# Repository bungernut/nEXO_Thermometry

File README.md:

# nNEXO_Microcontroller_Temp
Using Teensy 4.1 and Arduino Mega to collect temperatures using PT100's and thermocouples

This program requires several libraries to be compiled. 
All but the WDT is installable via the Arduino library manager. 
Since the project is built on a Teensy4.1 it also naturally also reduires Teensyduino.
- [ ] Adafruit BME280
- [ ] Adafruit MAX31865
- [ ] Adafruit MAX31856
- [ ] WDT_T4 (https://github.com/tonton81/WDT_T4)

Current TODO:
- Fix NativeEthernet locking issue
- Prevent LCD burn in (partially done)
- Issue with assigning IP to multiple devices, should have put a couple dip switches to assign mac or IP

Future feature adds:
- Utilize ILI9341 touch feature for interactive display

Schematic of PCB

PCBnew

PCB Version 1.2  
https://oshpark.com/shared_projects/bG9Ms06A (untested)

Parts:

| LOC | Part | Digikey PN |
| -- | -- | -- |
| J1 |  DB15 | LD15S33E4GV00LF-ND |
| J2 | Barrel 2x5.5mm | CP-002A-ND |
|Teensy Conn| 24POS RCPT| SAM1093-24-ND|
|Teensy Conn| 6POS 2mm RCPT| DUPIIN - 2141-2X03G00SB |
|Teensy header| 30POS 2.54mm | S1012EC-30-ND |
|Teensy header| 6POS 2mm | WM20513-ND |
| Ethernet Conn | 100 Base T | 1278-1052-ND |
| LCD Conn | 2x CONN HEADER 14POS | AE11367-ND|
| R1-12 | 22 Ohm 0805 | A126437CT-ND |
| R13 | 0 Ohm 0805 | A106066CT-ND |
| CP1 | 47 uF 1206 | 490-16309-1-ND |
| F1 | 1A Fuse | F6777CT-ND |
| C1 | 0.1 uF Ethernet Cap | BC1084CT-ND |
| MCU1 | 2x 24POS Recpt | SAM1093-24-ND |

### - Sensor Boards
| Board Type | Purpose | Digikey Pin |
| -- | -- | -- |
| Adafruit MAX31865 | RTD | 1528-1804-ND |
| Adafruit MAX31856 | Thermocouple Amplifier | 1528-1772-ND |
| Adafruit BME 280 | Temperature, Humidity, Pressure | 1528-1359-ND |

### - Microcontroller

Teensy 4.1 -
  - 1568-DEV-16771-ND

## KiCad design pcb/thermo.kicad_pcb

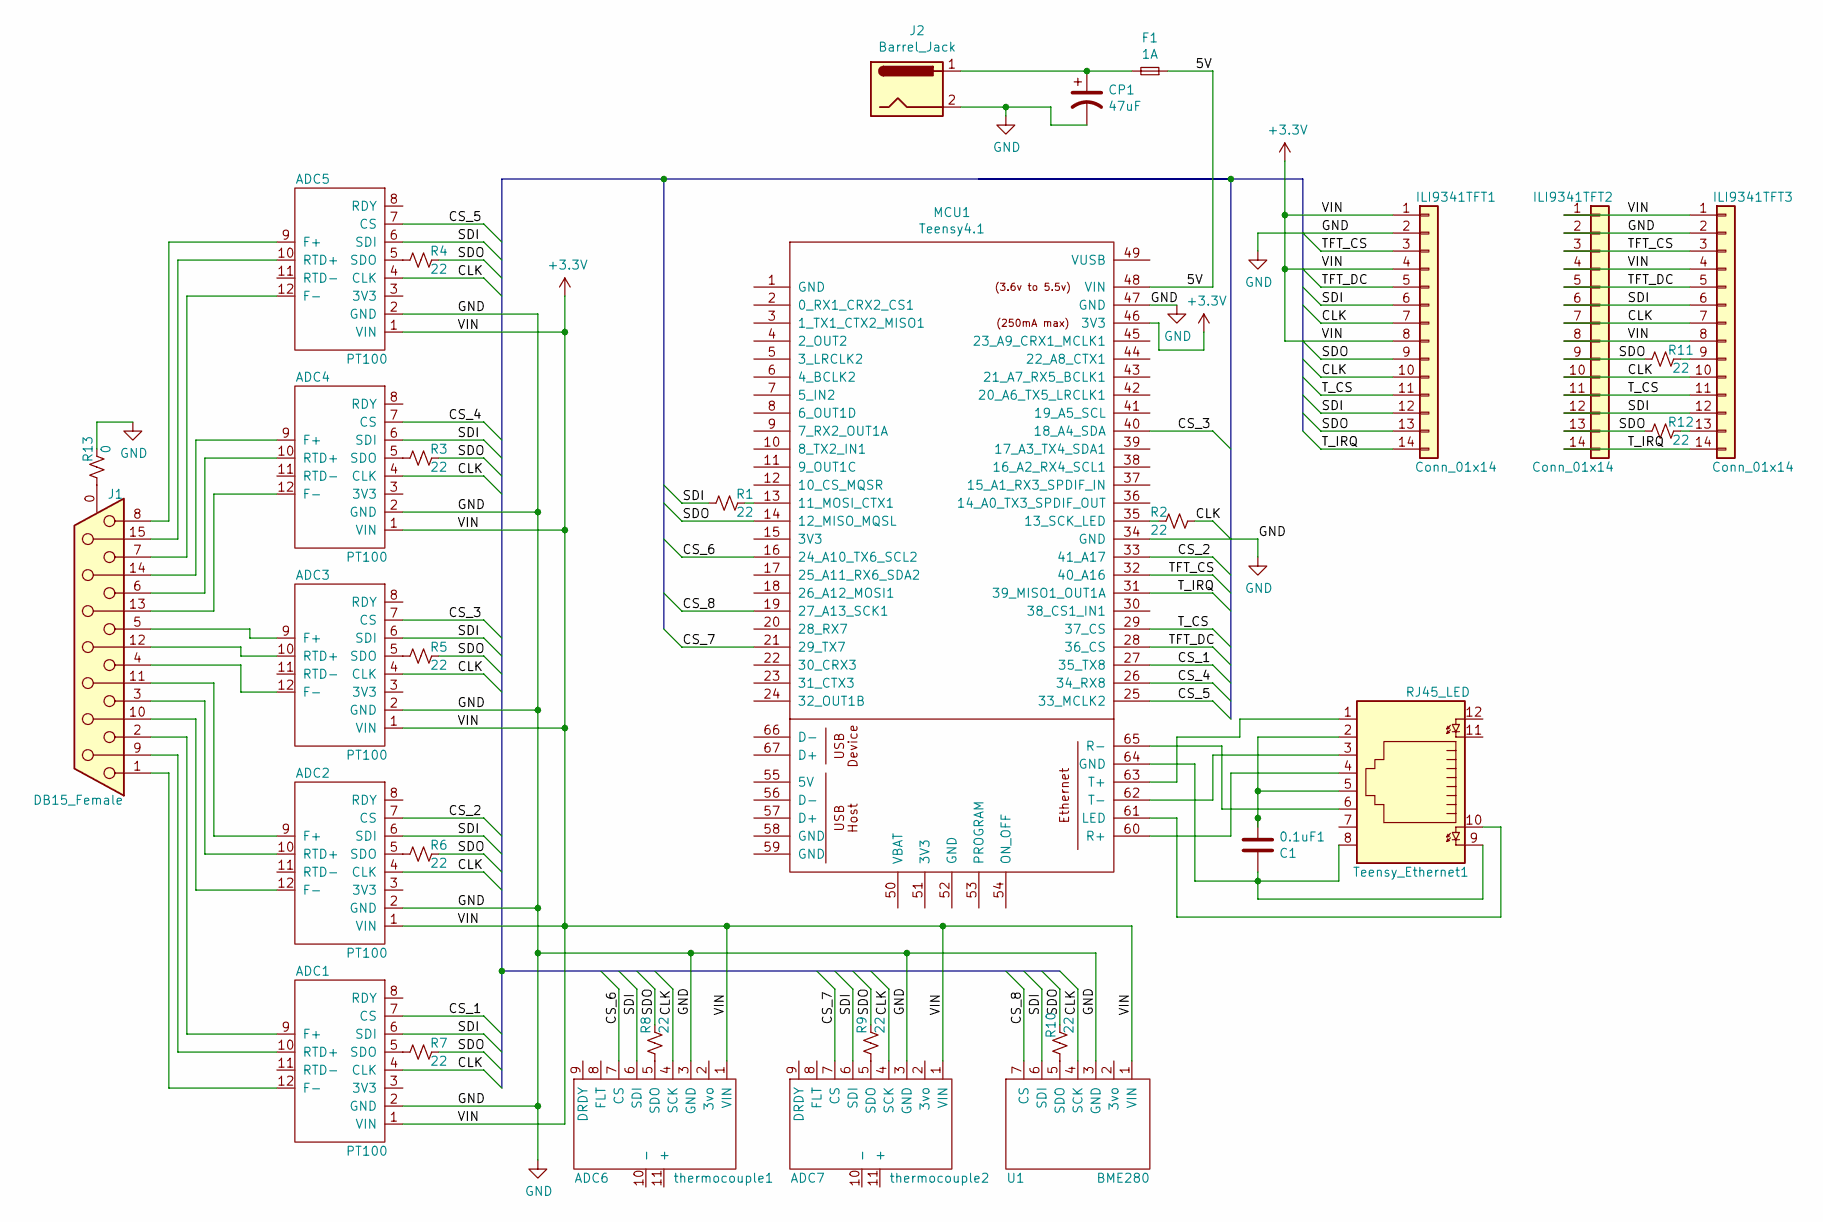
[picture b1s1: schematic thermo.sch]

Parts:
0.1uF1: C1; C_Disc_D3.0mm_W1.6mm_P2.50mm
ADC1, ADC2, ADC3, ADC4, ADC5: PT100; MAX31865
ADC6: thermocouple1; MAX31856
ADC7: thermocouple2; MAX31856
CP1: 47uF; CP_Radial_D5.0mm_P2.00mm
F1: 1A; thermo_fuse
ILI9341TFT1, ILI9341TFT2: Conn_01x14; ILI9341_2x7_connector
ILI9341TFT3: Conn_01x14; ILI9341_1x14_connector
J1: DB15_Female; D15_Female_Horizontal
J2: Barrel_Jack; BarrelJack_Horizontal
MCU1: Teensy4.1; Teensy41
R1, R2, R3, R4, R5, R6, R7, R8, R9, R10, R11, R12: 22; R_0805_2012Metric_Pad1.20x1.40mm_HandSolder
R13: 0; R_0805_2012Metric_Pad1.20x1.40mm_HandSolder
Teensy_Ethernet1: RJ45_LED; RJ45_Cetus_J1B1211CCD_Horizontal
U1: BME280

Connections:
+3V3: ADC1.1 (VIN), ADC2.1 (VIN), ADC3.1 (VIN), ADC4.1 (VIN), ADC5.1 (VIN), ADC6.1 (VIN), ADC7.1 (VIN), ILI9341TFT1.1, ILI9341TFT1.4, ILI9341TFT1.8, ILI9341TFT2.1, ILI9341TFT2.4, ILI9341TFT2.8, ILI9341TFT3.1, ILI9341TFT3.4, ILI9341TFT3.8, MCU1.46 (3V3), U1.1 (VIN)
/5V: F1.1, MCU1.48 (VIN)
/CLK: ADC1.4 (CLK), ADC2.4 (CLK), ADC3.4 (CLK), ADC4.4 (CLK), ADC5.4 (CLK), ADC6.4 (SCK), ADC7.4 (SCK), ILI9341TFT1.7, ILI9341TFT1.10, ILI9341TFT2.7, ILI9341TFT2.10, ILI9341TFT3.7, ILI9341TFT3.10, R2.1, U1.4 (SCK)
/CS_1: ADC1.7 (CS), MCU1.27 (35_TX8)
/CS_2: ADC2.7 (CS), MCU1.33 (41_A17)
/CS_3: ADC3.7 (CS), MCU1.40 (18_A4_SDA)
/CS_4: ADC4.7 (CS), MCU1.26 (34_RX8)
/CS_5: ADC5.7 (CS), MCU1.25 (33_MCLK2)
/CS_6: ADC6.7 (CS), MCU1.16 (24_A10_TX6_SCL2)
/CS_7: ADC7.7 (CS), MCU1.21 (29_TX7)
/CS_8: MCU1.19 (27_A13_SCK1), U1.7 (CS)
/SDI: ADC1.6 (SDI), ADC2.6 (SDI), ADC3.6 (SDI), ADC4.6 (SDI), ADC5.6 (SDI), ADC6.6 (SDI), ADC7.6 (SDI), ILI9341TFT1.6, ILI9341TFT1.12, ILI9341TFT2.6, ILI9341TFT2.12, ILI9341TFT3.6, ILI9341TFT3.12, R1.2, U1.6 (SDI)
/SDO: ILI9341TFT1.9, ILI9341TFT1.13, ILI9341TFT2.9, ILI9341TFT2.13, MCU1.14 (12_MISO_MQSL), R3.1, R4.1, R5.1, R6.1, R7.1, R8.1, R9.1, R10.1, R11.2, R12.2
/TFT_CS: ILI9341TFT1.3, ILI9341TFT2.3, ILI9341TFT3.3, MCU1.32 (40_A16)
/TFT_DC: ILI9341TFT1.5, ILI9341TFT2.5, ILI9341TFT3.5, MCU1.28 (36_CS)
/T_CS: ILI9341TFT1.11, ILI9341TFT2.11, ILI9341TFT3.11, MCU1.29 (37_CS)
/T_IRQ: ILI9341TFT1.14, ILI9341TFT2.14, ILI9341TFT3.14, MCU1.31 (39_MISO1_OUT1A)
GND: ADC1.2 (GND), ADC2.2 (GND), ADC3.2 (GND), ADC4.2 (GND), ADC5.2 (GND), ADC6.3 (GND), ADC7.3 (GND), CP1.2, ILI9341TFT1.2, ILI9341TFT2.2, ILI9341TFT3.2, J2.2, MCU1.34 (GND), MCU1.47 (GND), R13.1, U1.3 (GND)
unnamed: 0.1uF1.1, Teensy_Ethernet1.2, Teensy_Ethernet1.5
unnamed: 0.1uF1.2, MCU1.64 (GND), Teensy_Ethernet1.8, Teensy_Ethernet1.9
unnamed: ADC1.5 (SDO), R7.2
unnamed: ADC1.9 (F+), J1.2
unnamed: ADC1.10 (RTD+), J1.9
unnamed: ADC1.12 (F-), J1.1
unnamed: ADC2.5 (SDO), R6.2
unnamed: ADC2.9 (F+), J1.11 (P111)
unnamed: ADC2.10 (RTD+), J1.3
unnamed: ADC2.12 (F-), J1.10
unnamed: ADC3.5 (SDO), R5.2
unnamed: ADC3.9 (F+), J1.5
unnamed: ADC3.10 (RTD+), J1.12
unnamed: ADC3.12 (F-), J1.4
unnamed: ADC4.5 (SDO), R3.2
unnamed: ADC4.9 (F+), J1.14
unnamed: ADC4.10 (RTD+), J1.6
unnamed: ADC4.12 (F-), J1.13
unnamed: ADC5.5 (SDO), R4.2
unnamed: ADC5.9 (F+), J1.8
unnamed: ADC5.10 (RTD+), J1.15
unnamed: ADC5.12 (F-), J1.7
unnamed: ADC6.5 (SDO), R8.2
unnamed: ADC7.5 (SDO), R9.2
unnamed: CP1.1, F1.2, J2.1
unnamed: ILI9341TFT3.9, R11.1
unnamed: ILI9341TFT3.13, R12.1
unnamed: J1.0 (PAD), R13.2
unnamed: MCU1.13 (11_MOSI_CTX1), R1.1
unnamed: MCU1.35 (13_SCK_LED), R2.2
unnamed: MCU1.60 (R+), Teensy_Ethernet1.4
unnamed: MCU1.61 (LED), Teensy_Ethernet1.10
unnamed: MCU1.62 (T-), Teensy_Ethernet1.3
unnamed: MCU1.63 (T+), Teensy_Ethernet1.1
unnamed: MCU1.65 (R-), Teensy_Ethernet1.6
unnamed: R10.2, U1.5 (SDO)

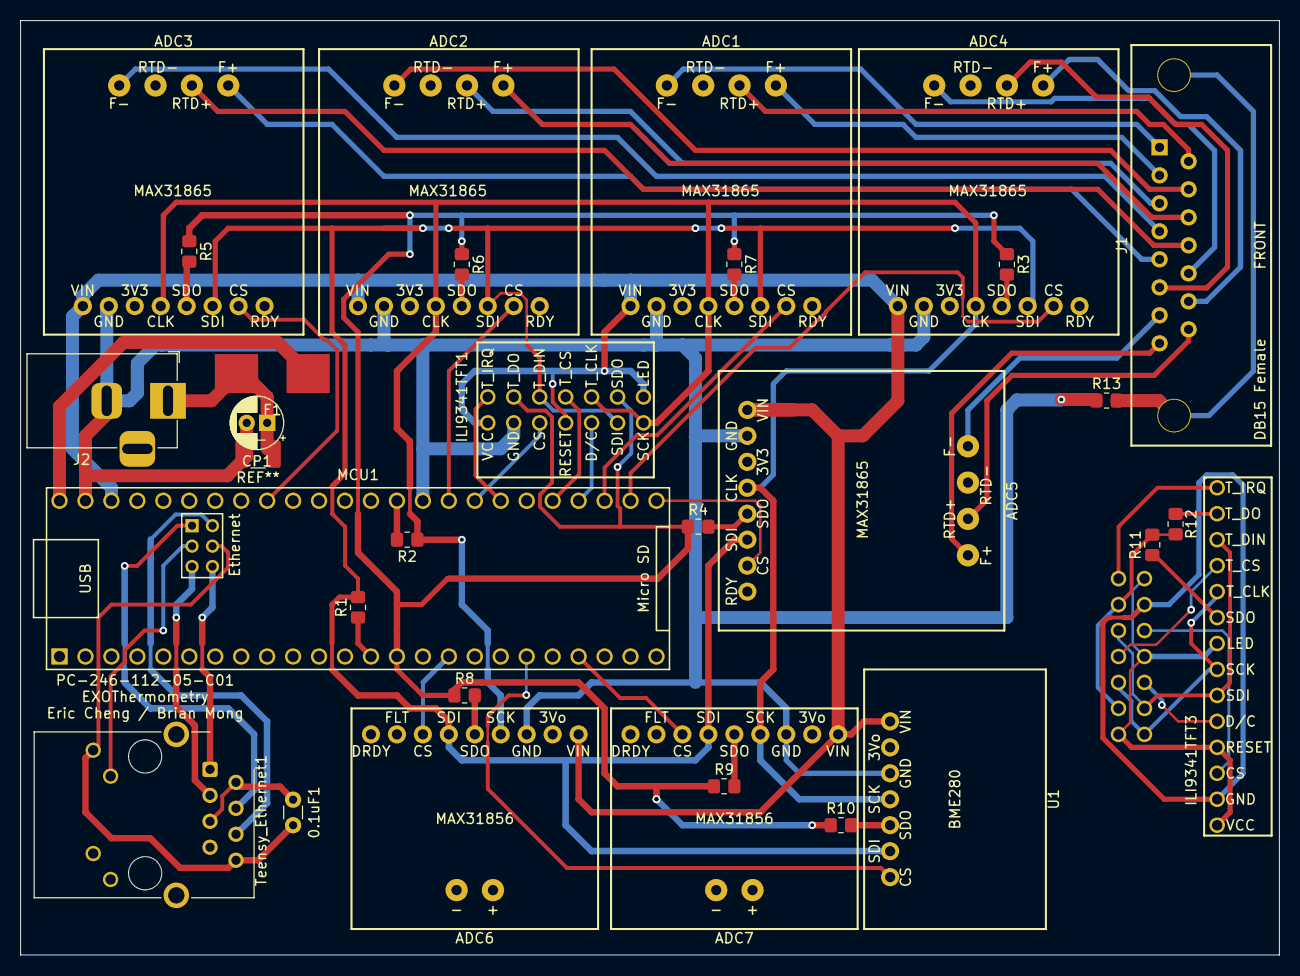
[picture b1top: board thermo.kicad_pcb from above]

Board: 2 copper layers, 123.2 x 91.4 mm, 31 parts (1 on the bottom side), 54 nets.

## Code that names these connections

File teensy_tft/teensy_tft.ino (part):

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Adafruit_BME280 bme(27); // hardware SPI

#define VERSION "nEXO Thermometry v1.4"
#define TFT_DC 36
#define TFT_CS 40
#define T_CS 37
#define T_IRQ 39
ILI9341_t3 tft = ILI9341_t3(TFT_CS, TFT_DC);

// Enter a MAC address for your controller below.
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
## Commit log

2022-02-15 cleaning up code with functions, feature added to not show temps if a fault is present
2022-02-15 added fault detection to modbus registers, writes 0 if fault detected on PT100 ADCs
2022-02-16 fixed MAX31865 sensor side pinout mixup, new layout on OSHPark V2
2022-02-22 Update README.md
    Updating to new board and adding some documentation
2022-02-22 Added watchdog to hopefully reset if ever frozen
2022-02-23 Still debugging WDT, definetly still broken
2022-04-13 added bme values to tft and modbus
2022-04-13 debugging BME280
2022-04-13 debugging, but the main issue was probably on nodered side
